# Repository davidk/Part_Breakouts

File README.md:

# Part Breakouts

These part breakouts are general purpose and most do not belong
in their own dedicated repository.

# Prototyping

Most of these boards are designed to be quickly fabricated using a CNC mill (currently an Othermachine Othermill v2).

This means the boards/parts have been tested with:

* FR-1 substrate (will not survive extended rework/reflow/shearing mechanical stresses)

* Usually built around wide trace/spacing rules for fast milling
  1/32 (usually) bit use.

Designs here try to minimize use of:

* Through-holes (a mill as of 2015 does not come with a plating bath)

* Vias

* Double sided designs (edge finding/registration makes things harder on 'go fast' prototypes)

# License

Unless otherwise specified for some reason, the breakouts in this repository are [CC0 1.0 Universal](https://creativecommons.org/publicdomain/zero/1.0/)

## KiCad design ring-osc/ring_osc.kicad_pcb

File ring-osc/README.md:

# Ring oscillator

A [ring oscillator](https://en.wikipedia.org/wiki/Ring_oscillator) that was used for a demo. Gerbers are setup for milling on FR-1. Please re-generate to fulfill your fab house's requirements if you're going that route.

(The little ears on the edges of the copper fill don't get milled off. The board isn't all that big, so there isn't much waste.)

## Parts used:

* 3x SN74LVC1GU04DBVR

* 2x 2-pin 2.54mm/0.1" headers (for input/output and power)

## Assembly

The ICs can be soldered by hand using a one-leg tack method. Solder one leg, straighten the IC slightly (as necessary),
and solder an opposing leg. Solder the rest, and heat up the first leg to relieve any strain.

For long term use it's probably best to go with solder paste+hot air reflow, and a proper PCB.

---

Solder in the headers too, but be sure to mark which output is which (since there won't be any silkscreen).

## License

[CC 1.0 Universal](https://creativecommons.org/publicdomain/zero/1.0/)

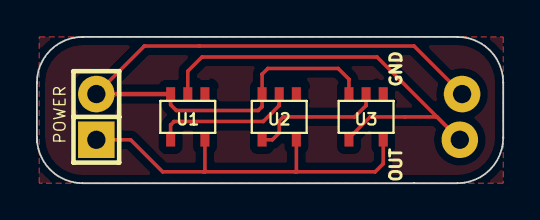
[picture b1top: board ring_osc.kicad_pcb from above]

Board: 2 copper layers, 25.9 x 8.1 mm, 6 parts (0 on the bottom side), 5 nets.

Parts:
GND1: CONN_1; 1pin
OUTPUT1: CONN_1; 1pin
POWER: BATTERY; Pin_Header_Straight_1x02
U1, U2, U3: 74AHC1G14; SOT23-5

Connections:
+3.3V: POWER.1, U1.5, U2.5, U3.5
GND: GND1.1, POWER.2, U1.3, U2.3, U3.3
unnamed: OUTPUT1.1, U1.2, U3.4
unnamed: U1.4, U2.2
unnamed: U2.4, U3.2

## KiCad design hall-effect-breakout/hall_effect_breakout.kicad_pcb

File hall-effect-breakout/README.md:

# Hall Effect Breakout (KiCAD)

This is a breakout board for the following hall effect ICs.

- AH180N-WG-7 | [Digikey](http://www.digikey.com/product-search/en?keywords=AH180N-WG-7DICT-ND)

- TCS40DLR,LF | [Digikey](http://www.digikey.com/product-search/en?keywords=TCS40DLRLFCT)

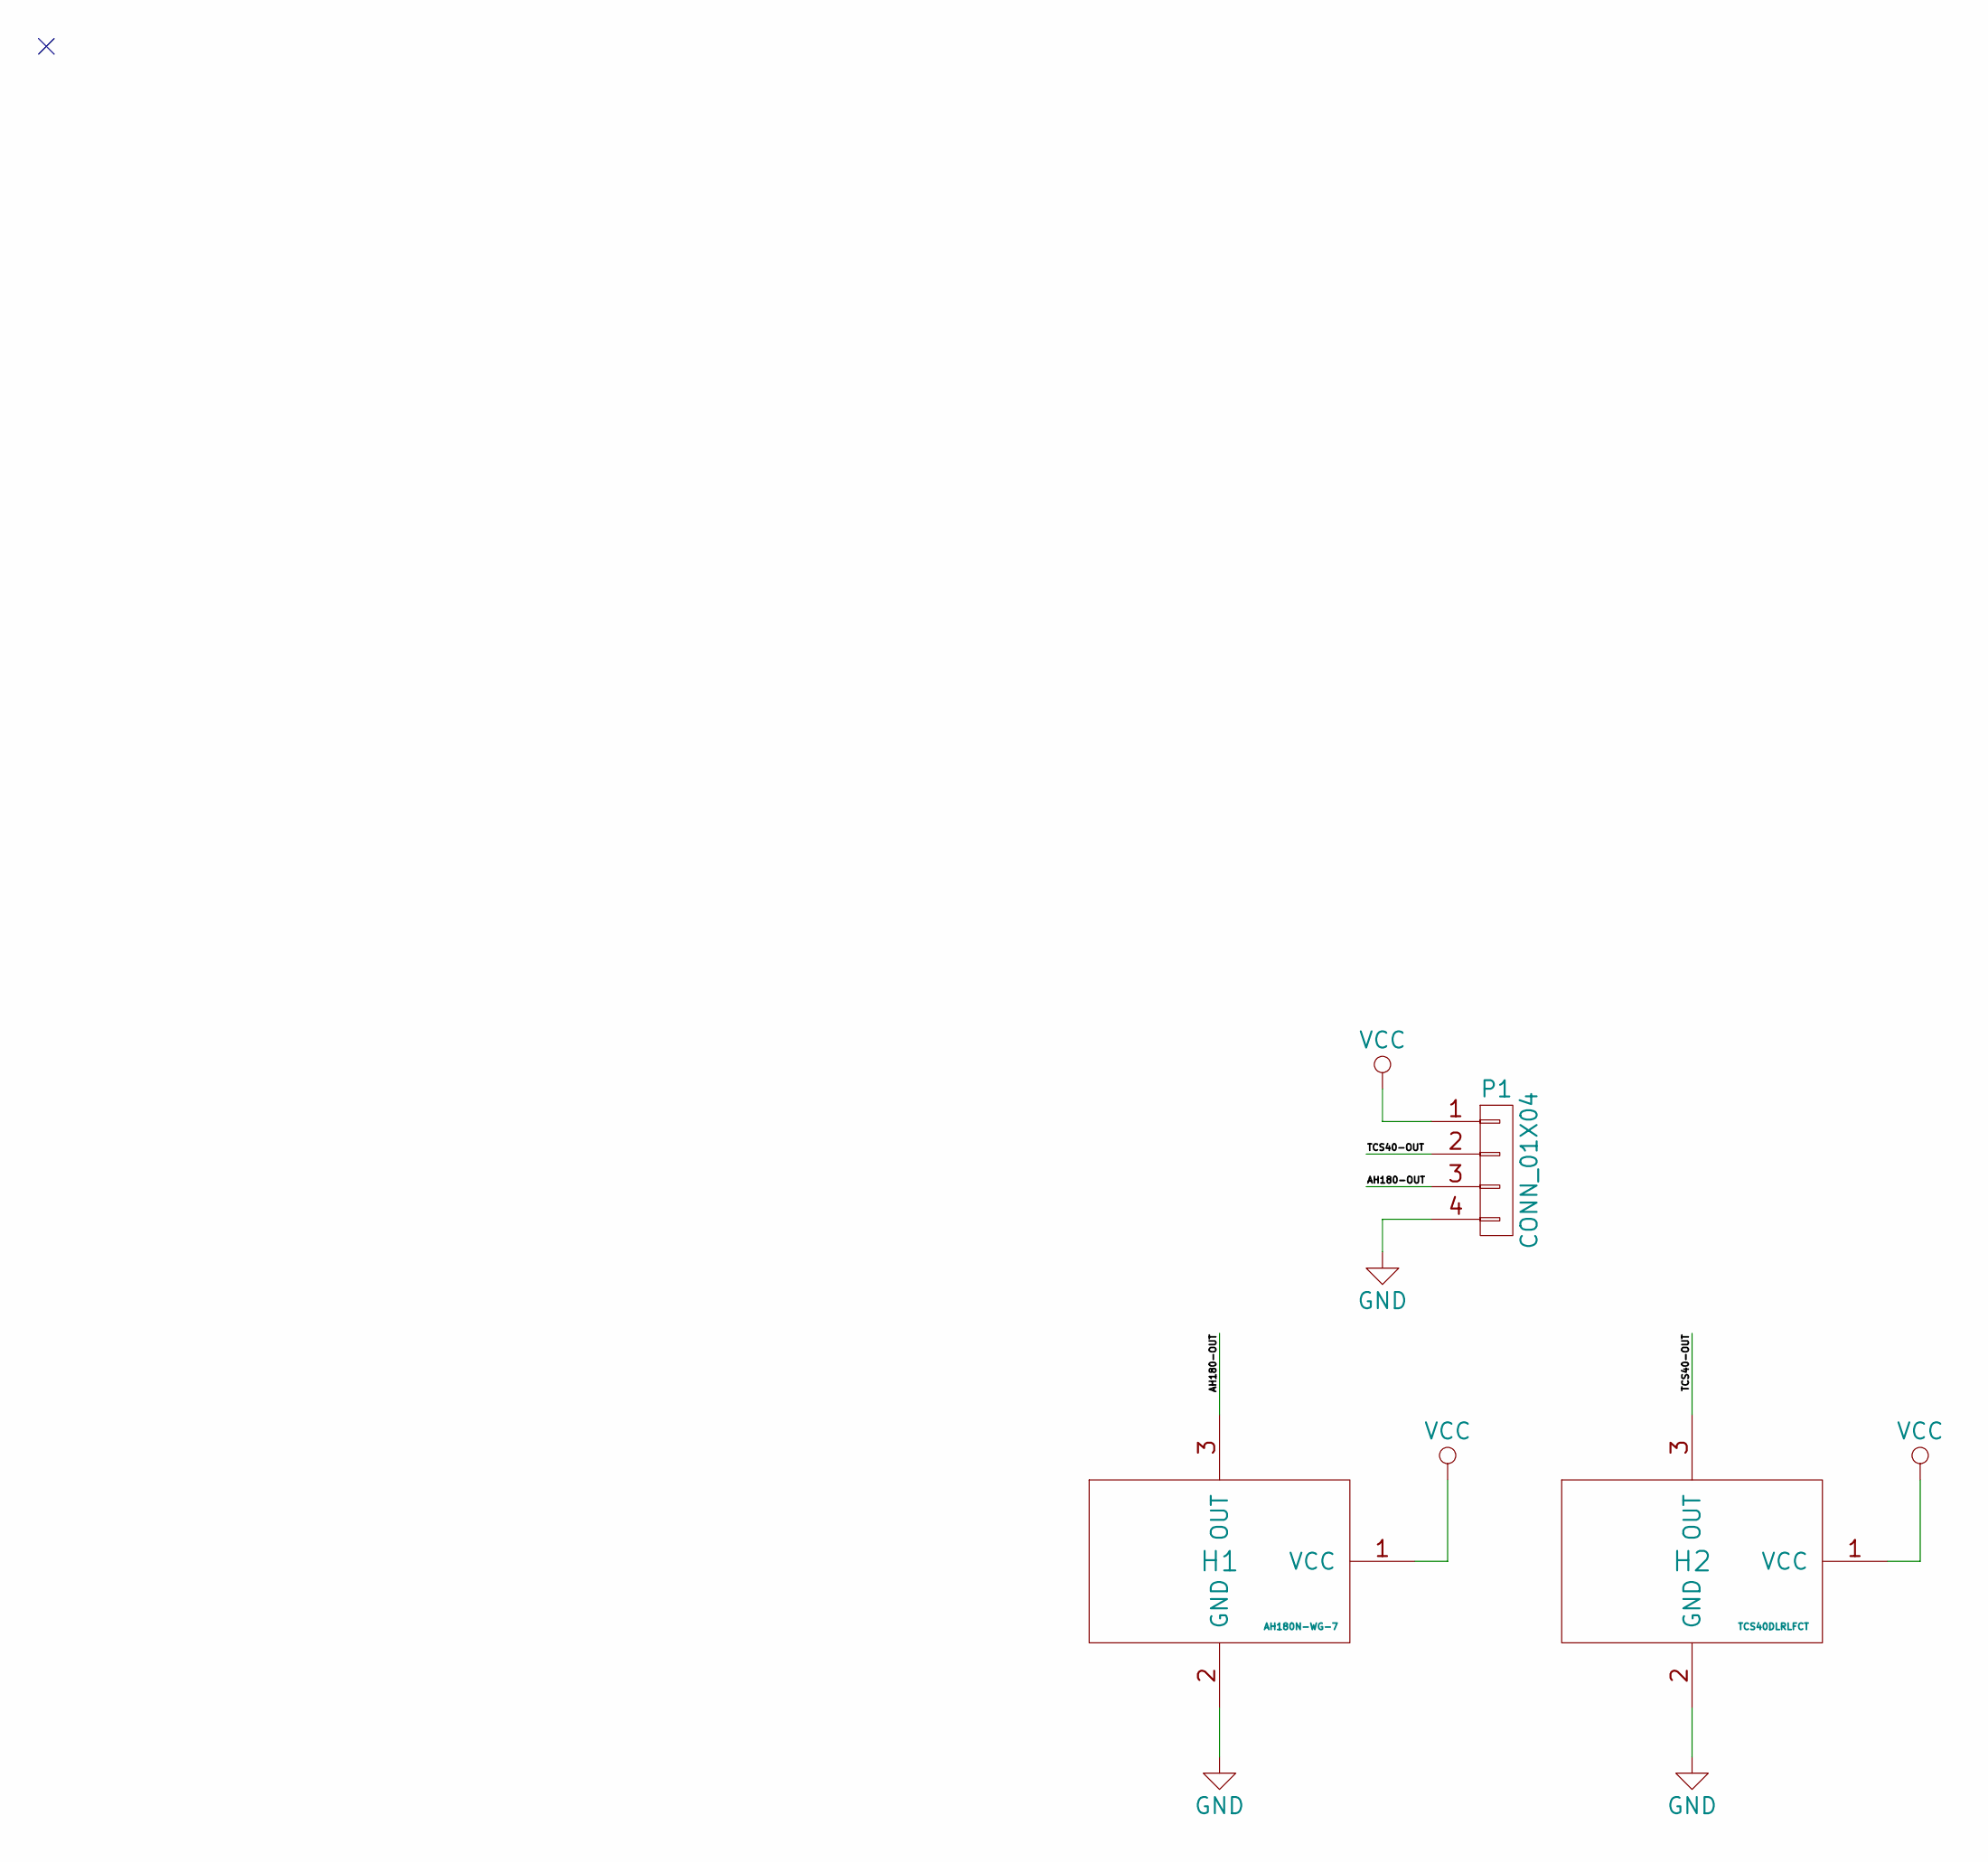
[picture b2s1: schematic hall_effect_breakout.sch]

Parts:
H1: AH180N-WG-7
H2: TCS40DLRLFCT; TCS40DLR,LF
P1: CONN_01X04; Pin_Header_Straight_1x04

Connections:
/AH180-OUT: H1.3 (OUT), P1.3
/TCS40-OUT: H2.3 (OUT), P1.2
GND: H1.2 (GND), H2.2 (GND), P1.4
VCC: H1.1 (VCC), H2.1 (VCC), P1.1

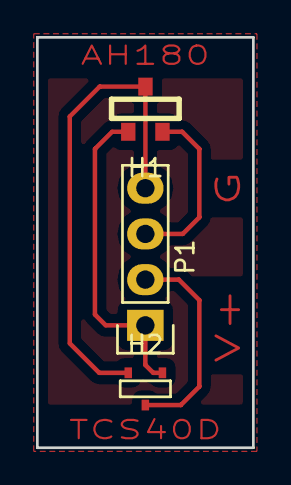
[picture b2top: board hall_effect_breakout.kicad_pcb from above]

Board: 2 copper layers, 12.0 x 22.8 mm, 3 parts (0 on the bottom side), 4 nets.

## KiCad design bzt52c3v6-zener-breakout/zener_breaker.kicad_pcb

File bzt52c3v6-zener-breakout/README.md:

# Zener Breakout

This is a breakout board for 4 [BZT52C3V6](http://www.diodes.com/_files/datasheets/ds18004.pdf) (pdf warning) zener diodes (they're packaged
as SOD123, so this should work for those too).

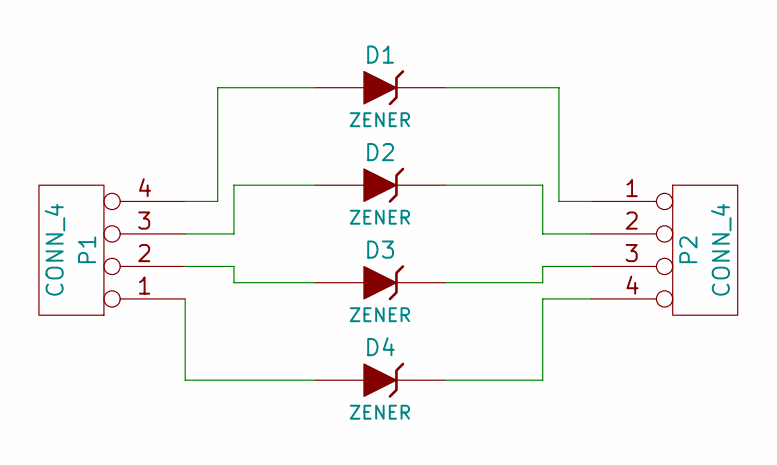
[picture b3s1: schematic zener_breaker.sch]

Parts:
D1, D2, D3, D4: ZENER
P1, P2: CONN_4

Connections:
unnamed: D2.1 (A), P1.3
unnamed: D3.1 (A), P1.2
unnamed: D4.1 (A), P1.1
unnamed: D1.2 (K), P2.1
unnamed: D2.2 (K), P2.2
unnamed: D3.2 (K), P2.3
unnamed: D4.2 (K), P2.4
unnamed: D1.1 (A), P1.4

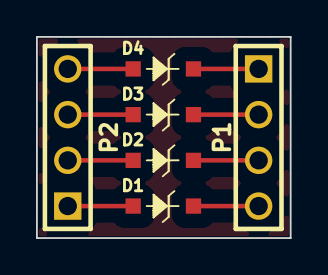
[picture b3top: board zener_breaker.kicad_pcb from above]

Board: 2 copper layers, 14.1 x 11.2 mm, 6 parts (0 on the bottom side), 8 nets.

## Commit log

2015-05-22 :boom::camel: Added .gitattributes
2015-05-22 Add breakout for the bzt52c3v6 3.6v zener diode
    Note: This has only been milled out, and not professionally fabricated,
    so some space is wasted in order to use a large bit (for speed/wear).
    Clearances and design rules are for a 1/32" bit.
2015-05-22 Ignore kicad .bak files
2015-05-22 Add a README for this repository
2016-10-03 Add Othermill DRC documentation
2016-10-03 Add hall effect sensor breakouts
2016-10-06 Add on-copper labels
2016-10-06 Add generated gerbers
2016-10-06 Adjust text tolerances
2016-10-26 Add a ring oscillator and associated gerbers
    This was a board from 2015, so information is sort of incomplete
    (like what bits I used for this, or where I put the PCB..)
    It was milled out and tested with a scope though. It works!
2016-10-26 ring_osc: Specify header type
2016-10-26 Add a board screenshot and README
2016-10-26 Change _ to - (for ring_osc)
2016-10-26 Create LICENSE
2017-06-16 Add README from https://raw.githubusercontent.com/github/gitignore/master/KiCad.gitignore
2017-06-16 Add gitignore for KiCAD
    Sourced from: https://raw.githubusercontent.com/github/gitignore/master/KiCad.gitignore
2017-06-16 Add 3.5mm jack breakout
